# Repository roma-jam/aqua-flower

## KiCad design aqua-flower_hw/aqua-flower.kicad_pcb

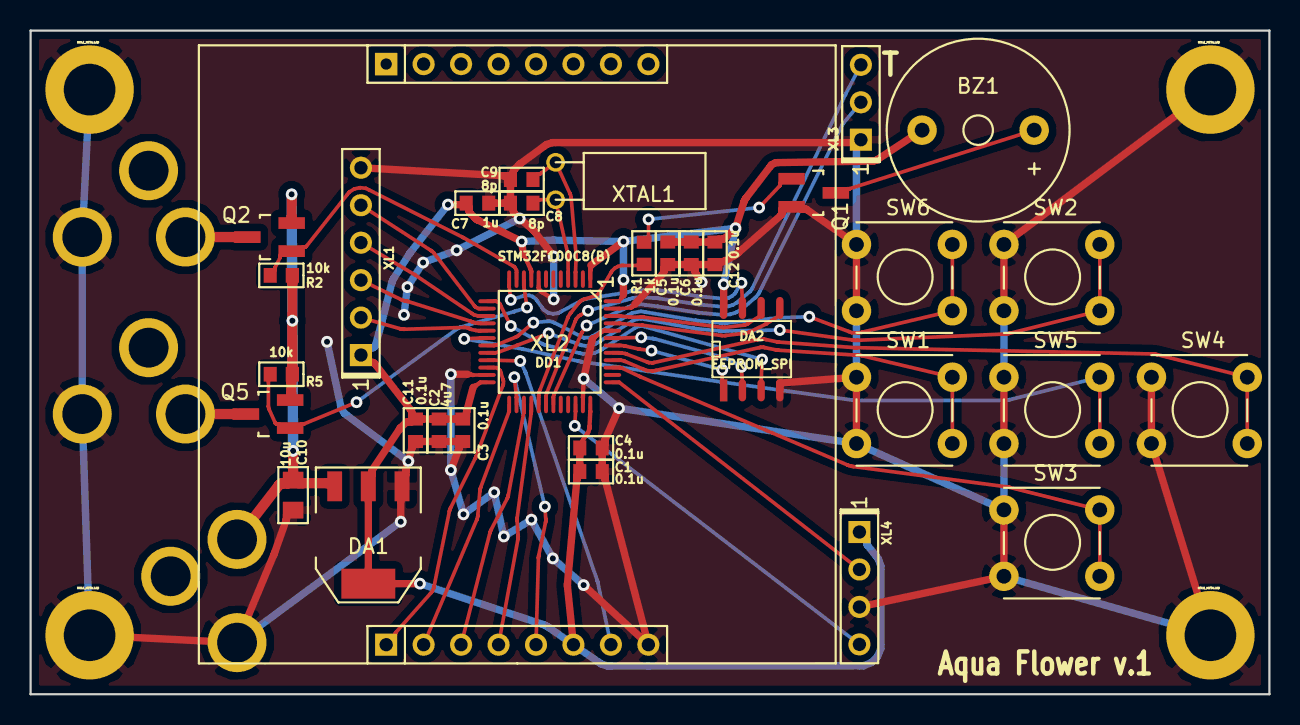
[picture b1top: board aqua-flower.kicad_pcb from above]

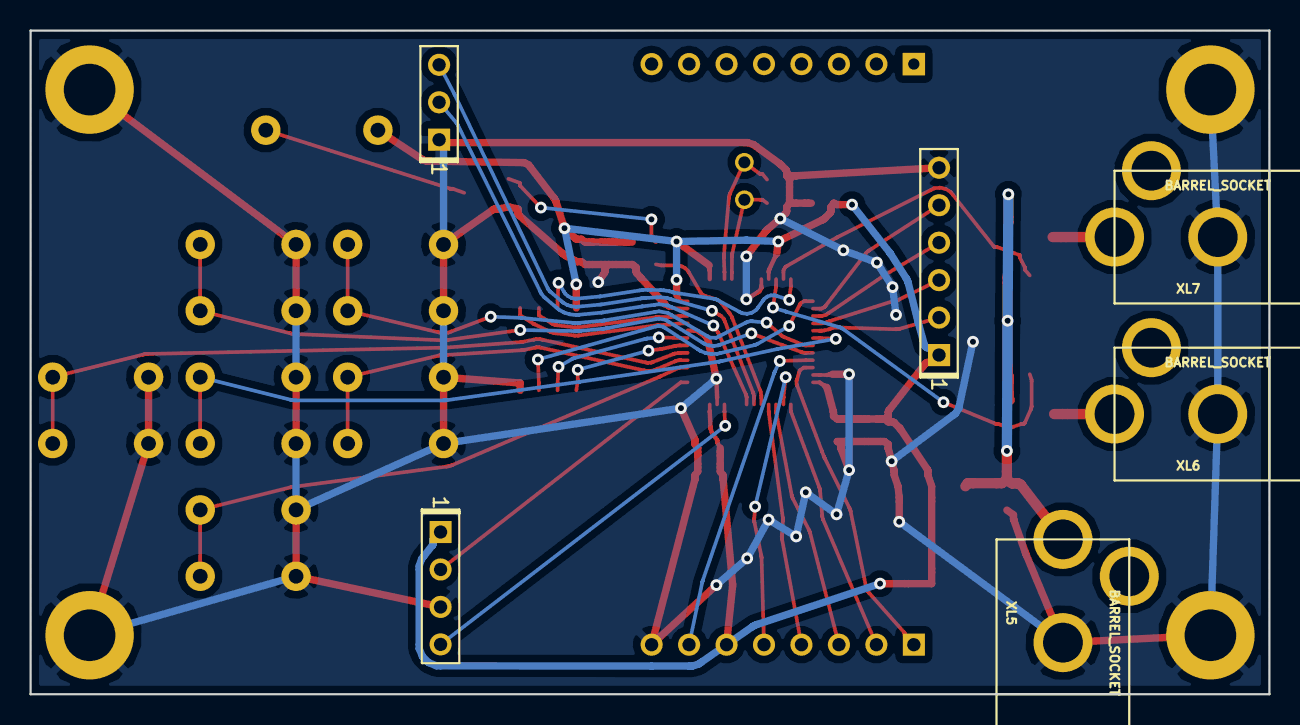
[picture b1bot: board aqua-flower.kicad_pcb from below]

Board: 2 copper layers, 84.0 x 45.0 mm, 40 parts (3 on the bottom side), 38 nets.

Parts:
BZ1: BUZZER; Buzzer_12x9.5RM7.6
C1, C3, C4, C5, C6, C11, C12: 0.1u; CAP_0603
C2: 4u7; CAP_0603
C7: 1u; CAP_0603
C8, C9: 8p; CAP_0603
C10: 10u; CAP_0805
DA1: LD1117; SOT-223
DA2: EEPROM_SPI; SO8
DD1: STM32F100C8(B); LQFP48
HOLE1, HOLE2, HOLE3, HOLE4: HOLE_METALLED; Hole3_5_out6mm
Q1: NPN; SOT-23_Handsoldering
Q2, Q5: IRLML6302; SOT-23_Handsoldering
R1: 1k; RES_0603
R2, R5: 10k; RES_0603
SW1, SW2, SW3, SW4, SW5, SW6: BUTTON; PUSH_THRHOLE_3-1825910-5
XL1: CONN_6; PLS-6
XL2: CONN_8; 84x48_LCD_Module
XL3: CONN_3; PLS-3
XL4: ST_SWD; PLS-4
XL5, XL6, XL7: BARREL_SOCKET; Barrel
XTAL1: CRYSTAL; Crystal_Watch

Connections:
+3.3V: BZ1.2, C1.1, C2.1, C3.1, C4.1, C5.1, C6.1, C7.1, C11.1, C12.1, DA1.2, DA1.4, DA2.8, DD1.1, DD1.9, DD1.24, DD1.36, DD1.48, XL1.1, XL2.6, XL4.1
+12V: C10.1, DA1.3, Q2.2, Q5.2, R2.1, R5.1, XL5.PWR
/BTN_CANCEL: DD1.19, SW6.2
/BTN_DOWN: DD1.39, SW3.2
/BTN_LEFT: DD1.40, SW1.2
/BTN_OK: DD1.18, SW5.2
/BTN_RIGHT: DD1.41, SW4.2
/BTN_UP: DD1.20, SW2.2
/BUZZER: DD1.29, R1.2
/CC_CS: DD1.14, XL1.5
/CC_MISO: DD1.16, XL1.3
/CC_MOSI: DD1.17, XL1.2
/CC_SCK: DD1.15, XL1.4
/CH1_POWER: DD1.10, Q5.1, R5.2
/CH2_POWER: DD1.11, Q2.1, R2.2
/DBG_RX: DD1.31, XL3.2
/DBG_TX: DD1.30, XL3.3
/EE_CS: DA2.1, DD1.42
/EE_HOLD: DA2.7, DD1.12
/EE_MISO: DA2.2, DD1.43
/EE_MOSI: DA2.5, DD1.45
/EE_SCK: DA2.6, DD1.46
/EE_WP: DA2.3, DD1.13
/LCD_BCKLT: DD1.21, XL2.7
/LCD_CE: DD1.25, XL2.2
/LCD_CLK: DD1.26, XL2.5
/LCD_DC: DD1.27, XL2.3
/LCD_DIN: DD1.28, XL2.4
/LCD_RESET: DD1.22, XL2.1
/PUMP1: Q5.3, XL6.PWR
/PUMP2: Q2.3, XL7.PWR
/SWCLK: DD1.37, XL4.2
/SWDIO: DD1.34, XL4.4
GND: C1.2, C2.2, C3.2, C4.2, C5.2, C6.2, C7.2, C8.2, C9.2, C10.2, C11.2, C12.2, DA1.1, DA2.4, DD1.8, DD1.23, DD1.35, DD1.44, DD1.47, HOLE1.H, HOLE2.H, HOLE3.H, HOLE4.H, Q1.2, SW1.1, SW2.1, SW3.1, SW4.1, SW5.1, SW6.1, XL1.6, XL2.8, XL3.1, XL4.3, XL5.GND, XL6.GND, XL7.GND
unnamed: BZ1.1, Q1.3
unnamed: C8.1, DD1.4, XTAL1.1
unnamed: C9.1, DD1.3, XTAL1.2
unnamed: Q1.1, R1.1

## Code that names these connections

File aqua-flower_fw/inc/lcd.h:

/*
 * lcd.h
 *
 *  Created on: 27.10.2013
 *      Author: Roma Jam
 */

#ifndef LCD_H_
#define LCD_H_

#include <stdarg.h>
#include "kl_lib_f100.h"
#include "lcd_font.h"
#include "clock_digits.h"
#include "clock.h"
#include "config.h"

//#define ENABLE_DMA_MODE

#define REFRESH_TIME_MS             121

// ==== GPIOS ====
//#define LCD_SPI                   SPI2
#define LCD_TIM                     TIM2
#define LCD_GPIO		            GPIOB

#define LCD_BCKLT                   10
#define LCD_RESET                   11
#define LCD_CE                      12
#define LCD_SCLK                    13
#define LCD_DC                      14
#define LCD_DIN                     15

#define LCD_STR_HEIGHT              8
#define LCD_STR_WIDTH               16

#define LCD_WIDTH                   84
#define LCD_HEIGHT                  48
// Data sizes
#define LCD_VIDEOBUF_SIZE           (uint32_t)((LCD_WIDTH*LCD_HEIGHT) >> 3)     // =  84*48/8

#define LCD_DEFAULT_BACKLIGTH       15

#ifdef LCD_SPI
#define SPI_MODE    SPI_CR1_SSM |       /* NSS Software Managment Enable */    \
                    SPI_CR1_SSI |       /* Internal slave select */            \
                    SPI_CR1_CPHA |      /* 2 Edge */                           \
                    SPI_CR1_MSTR        /* Master Configuration */             \

enum brDiv_t {
    brDiv2   = 0b000,
    brDiv4   = 0b001,
    brDiv8   = 0b010,
    brDiv16  = 0b011,
    brDiv32  = 0b100,
    brDiv64  = 0b101,
    brDiv128 = 0b110,
    brDiv256 = 0b111
};
#endif

// LCD Commands
#define PCD8544_POWERDOWN 0x04
#define PCD8544_ENTRYMODE 0x02
#define PCD8544_EXTENDEDINSTRUCTION 0x01

#define PCD8544_DISPLAYBLANK 0x0
#define PCD8544_DISPLAYNORMAL 0x4
#define PCD8544_DISPLAYALLON 0x1
#define PCD8544_DISPLAYINVERTED 0x5

// H = 0
#define PCD8544_FUNCTIONSET 0x20
#define PCD8544_DISPLAYCONTROL 0x08
#define PCD8544_SETYADDR 0x40
#define PCD8544_SETXADDR 0x80

// H = 1
#define PCD8544_SETTEMP 0x04
#define PCD8544_SETBIAS 0x10
#define PCD8544_SETVOP 0x80

enum PseudoGraph_t {
    CornerTopLeftDouble = 0x99,
    CornerTopRightDouble = 0x8B,
    CornerBottomLeftDouble = 0x98,
    CornerBottomRightDouble = 0x8C,
    LineHorizDouble = 0x9D,
    LineHorizDoubleUp = 0x9A,
    LineHorizDoubleDown = 0x9B,
    LineVertDouble = 0x8A,
    LineVertDoubleLeft = 0x89,
    LineVertDoubleRight = 0x9C,
    LineCrossDouble = 0x9E,
};

enum DrawMode_t {
	DRAW, // zero has no effect
	CLEAR, // zero has no effect, one clears
	OVERWRITE, // write both zeros and ones
	OVERWRITE_INVERTED, // write both with negated meaning
	INVERT // zero has no effect, one inverts
};

extern void LcdBackligthTmr(void *p);

class Lcd_t {
private:
    VirtualTimer Timer;
    uint16_t IBuf[LCD_VIDEOBUF_SIZE];
    bool ShouldUpdate;
    bool toggle;
    DrawMode_t DrawMode;
    // printf functions
    int __vsprintf(char *buf, const char *format, va_list args);
#ifdef LCD_SPI
    inline void SPI_SetBaud(brDiv_t brDiv)  { LCD_SPI->CR1 |= brDiv << 3;        }
#endif
    // Pin driving functions
    inline void InitGpios() {
        PinSetupOut(LCD_GPIO, LCD_RESET, omPushPull, ps50MHz);
        PinSetupOut(LCD_GPIO, LCD_CE, omPushPull, ps50MHz);
        PinSetupOut(LCD_GPIO, LCD_DC, omPushPull, ps50MHz);
        PinSetupAlterFuncOutput(LCD_GPIO, LCD_BCKLT, omPushPull, ps50MHz);
#ifdef LCD_SPI
        PinSetupAlterFuncOutput(LCD_GPIO, LCD_SCLK, omPushPull, ps50MHz);
        PinSetupAlterFuncOutput(LCD_GPIO, LCD_DIN, omPushPull, ps50MHz);
#else
        PinSetupOut(LCD_GPIO, LCD_SCLK, omPushPull, ps50MHz);
        PinSetupOut(LCD_GPIO, LCD_DIN, omPushPull, ps50MHz);
#endif
    }

    void RESET_Hi(void) { PinSet(LCD_GPIO, LCD_RESET);    }
    void RESET_Lo(void) { PinClear(LCD_GPIO, LCD_RESET);  }
    void DataMode(void){ PinSet(LCD_GPIO, LCD_DC);      }
    void CmdMode(void) { PinClear(LCD_GPIO, LCD_DC);    }
    void SCLK_Hi(void) { PinSet(LCD_GPIO, LCD_SCLK);    }
    void SCLK_Lo(void) { PinClear(LCD_GPIO, LCD_SCLK);  }
    void DIN_Hi (void) { PinSet(LCD_GPIO, LCD_DIN);     }
    void DIN_Lo (void) { PinClear(LCD_GPIO, LCD_DIN);   }
    void WriteCmd(uint8_t ACmd);
    void WriteData(uint8_t AData);
    // High-level
    void DrawBlock(uint32_t index, uint8_t data, uint8_t mask);
    void DrawChar(uint32_t *index, uint8_t AChar);

    // Clock
    void ClearDelimeter();
    void DrawDelimeter();
    void DrawClockDigit(uint8_t Pos, uint8_t Digit);
    void DelimeterToggle();
    void Backlight(uint8_t ABrightness)  { LCD_TIM->CCR3 = ABrightness; }

public:
    // IRQ
    void CS_Hi (void) { PinSet(LCD_GPIO, LCD_CE);     }
    void CS_Lo (void) { PinClear(LCD_GPIO, LCD_CE);   }
    // General use
    void Init(void);
    void Task(void);
    void Shutdown(void);


    void BacklightOn()
    {
        Backlight(LCD_DEFAULT_BACKLIGTH);
        chVTReset(&Timer);
        chVTSet(&Timer, MS2ST(LCD_DEFAULT_BACKLIGTH_MS), LcdBackligthTmr, nullptr);
    }
    void BacklightOff() { Backlight(0); }


    // High-level
    void SetDrawMode(DrawMode_t mode) { DrawMode = mode; }
    void SetX(uint8_t newX) { WriteCmd(PCD8544_SETXADDR | newX); }
    void SetY(uint8_t newY) { WriteCmd(PCD8544_SETYADDR | newY); }
    void Printf(uint32_t column, uint32_t row, const char *S, ...);
    void DrawImage(uint32_t x, uint32_t y, const uint8_t *img);

    void Cls(void) { for(uint16_t i=0; i < LCD_VIDEOBUF_SIZE; i++) IBuf[i] = 0x0000; }

    /* ==== Pseudographics ====
     *  Every command consists of PseudoGraph_t AChar, uint8_t RepeatCount.
     *  Example: LineHorizDouble, 11 => print LineHorizDouble 11 times.
     *  Cmds end up with 0.
     */
    void Symbols(int column, int row, ...);

    void PutPixel(int x, int y, int c) {
//    	assert(c == 0 || c == 1);
    	int index = x + (y/8)*LCD_WIDTH;
    	uint8_t mask = 1 << (7-y%8);
		DrawBlock(index, c ? mask : 0, mask);
    }

    friend class clock_t;
};

extern Lcd_t Lcd;
#endif /* LCD_H_ */

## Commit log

2016-03-16 Add HW project.
2016-03-18 Update PCB settings
2016-03-31 Place all pcb details and start to trace pcb.
2016-03-31 Reset Library Component
2016-03-31 Add holes
2016-03-31 Now everything is ok. + Add library by the library Wizard. + Found needed in KiCad github.
2016-03-31 Export to TopoR from KiCAD
2016-04-01 Add eeprom
2016-04-01 Replace straight pin connectors
2016-04-03 PCB finalize. Ready to production.
2016-04-04 Add rescue file.
2016-04-04 update gitignore list
2016-04-04 Fix silk
2016-04-06 Update silk
2016-04-07 Update PCB try to reach no error in rezonit
2016-04-07 follow up
2016-04-07 Started FW project. Add files
2016-04-08 Backlight works
2016-04-08 Try to start LCD
2016-04-10 LCD started OK + Fix fonts.
2016-04-10 + Buttons + Buzzer + eeprom + clocks
2016-04-10 + print clock_digit + clock_digit library
2016-04-10 Fix delimeter
2016-04-11 + Fix brigth + Fix "0" clock digit
2016-04-11 + digit "1"
2016-04-11 + clock digit "3" + delimeter toggle function
2016-04-12 + all digits + draw time
2016-04-14 Proceed clock
2016-04-14 Clock.CurrentTime.Update function complete.
2016-04-14 + Lcd DMA code + Lcd SPI code
2016-04-14 + Fix clock indicate and seconds counting + EEPROM Init done
2016-04-15 + Buttons logic
2016-04-16 RTC clock on 32.768kHz osc worked.
2016-04-17 + Clock done. + water pump configure.
2016-04-18 Update sch of pcb
2016-04-27 + Clock + Buttons + App Logic
2016-04-27 Fix bias voltage on LCD
2016-04-27 Setup Clock done
2016-04-28 Add lpc_rl library with LPC cpu
2016-04-28 + Clock inc seconds on IRQ + Water pump on/off logic
2016-04-28 + Config setup + Config in eeprom
2016-04-28 + Defines some lines
2016-04-28 + Fix seconds counter
2016-07-12 + Make test pump + Change pump vice versa
2016-11-10 Add test mode with button pressed
2017-01-16 Fix VOP lcd's
2017-01-16 Add hours and refactor water pump class.
2017-01-16 Add pdf file of PCB
